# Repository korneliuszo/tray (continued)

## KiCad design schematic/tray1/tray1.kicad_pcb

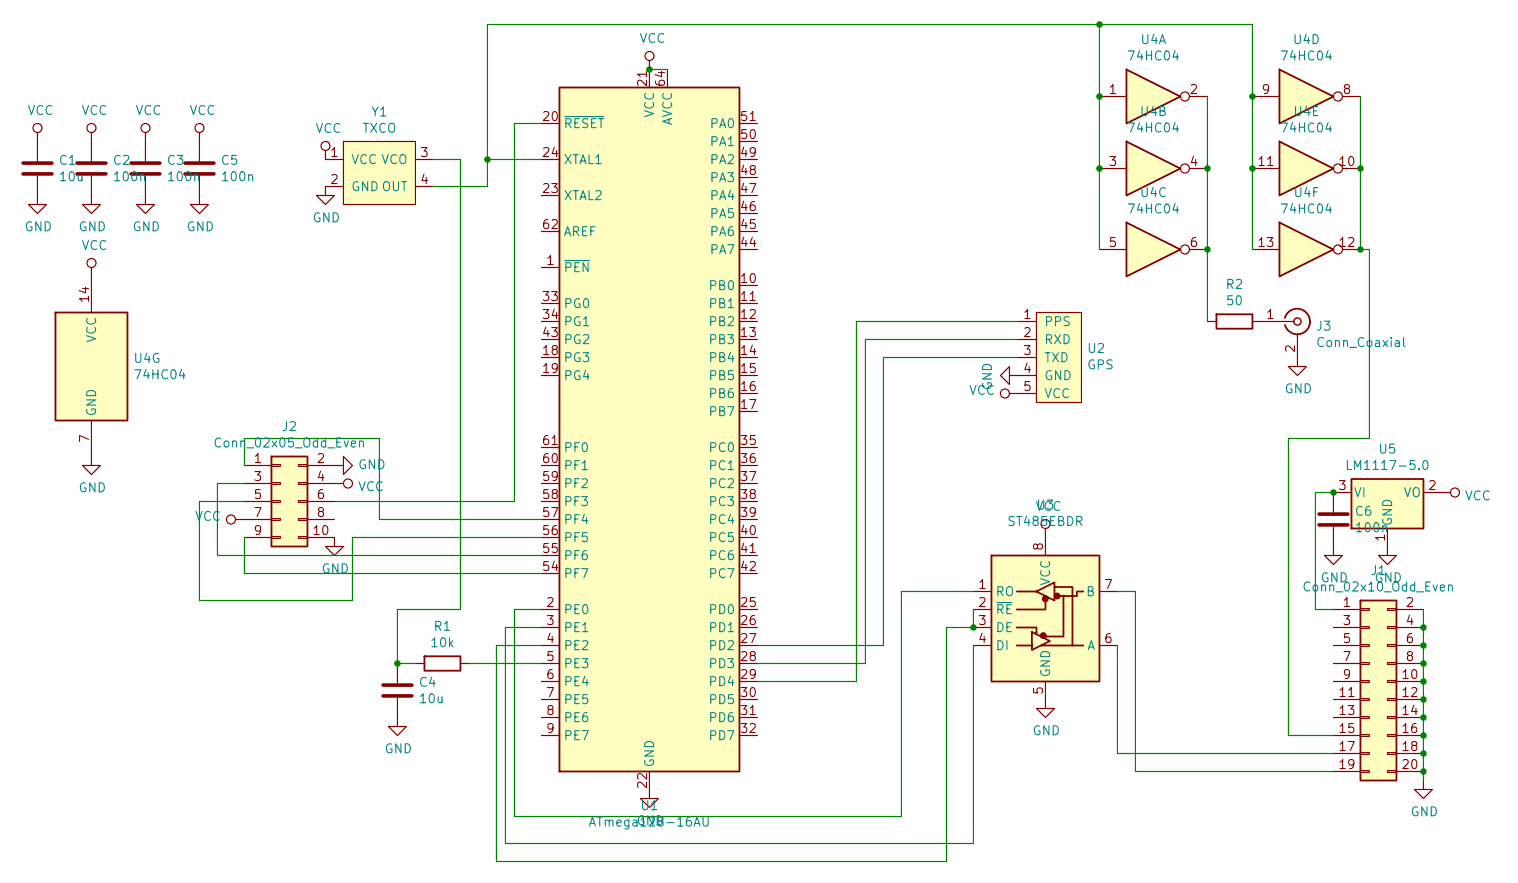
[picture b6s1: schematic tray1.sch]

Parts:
C1, C4: 10u; C_0805_2012Metric
C2, C3, C5: 100n; C_0805_2012Metric
C6: 100n; C_0805_2012Metric_Pad1.15x1.40mm_HandSolder
J1: Conn_02x10_Odd_Even; IDC-Header_2x10_P2.54mm_Horizontal
J2: Conn_02x05_Odd_Even; IDC-Header_2x05_P2.54mm_Vertical
J3: Conn_Coaxial; BNC_Amphenol_B6252HB-NPP3G-50_Horizontal
R1: 10k; R_0805_2012Metric
R2: 50; R_0805_2012Metric
U1: ATmega128-16AU; TQFP-64_14x14mm_P0.8mm
U2: GPS
U3: ST485EBDR; SOIC-8_3.9x4.9mm_P1.27mm
U4: 74HC04; SOIC-14_3.9x8.7mm_P1.27mm
U5: LM1117-5.0; SOT-223-3_TabPin2
Y1: TXCO; TCXO

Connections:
GND: C1.2, C2.2, C3.2, C4.2, C5.2, C6.2, J1.2, J1.4, J1.6, J1.8, J1.10, J1.12, J1.14, J1.16, J1.18, J1.20, J2.2, J2.10, J3.2 (Ext), U1.22 (GND), U1.53 (GND), U1.63 (GND), U2.4 (GND), U3.5 (GND), U4.7 (GND), U5.1 (GND), Y1.2 (GND)
unnamed: C4.1, R1.2, Y1.3 (VCO)
unnamed: C6.1, J1.1, U5.3 (VI)
unnamed: J1.15, U4.8, U4.10, U4.12
unnamed: J1.17, U3.6 (A)
unnamed: J1.19, U3.7 (B)
unnamed: J2.1, U1.57 (PF4)
unnamed: J2.3, U1.55 (PF6)
unnamed: J2.5, U1.56 (PF5)
unnamed: J2.6, U1.20 (~RESET)
unnamed: J2.9, U1.54 (PF7)
unnamed: J3.1 (In), R2.1
unnamed: R1.1, U1.5 (PE3)
unnamed: R2.2, U4.2, U4.4, U4.6
unnamed: U1.2 (PE0), U3.1 (RO)
unnamed: U1.3 (PE1), U3.4 (DI)
unnamed: U1.4 (PE2), U3.2 (~RE), U3.3 (DE)
unnamed: U1.24 (XTAL1), U4.1, U4.3, U4.5, U4.9, U4.11, U4.13, Y1.4 (OUT)
unnamed: U1.27 (PD2), U2.3 (TXD)
unnamed: U1.28 (PD3), U2.2 (RXD)
unnamed: U1.29 (PD4), U2.1 (PPS)
VCC: C1.1, C2.1, C3.1, C5.1, J2.4, J2.7, U1.21 (VCC), U1.52 (VCC), U1.64 (AVCC), U2.5 (VCC), U3.8 (VCC), U4.14 (VCC), U5.2 (VO), Y1.1 (VCC)

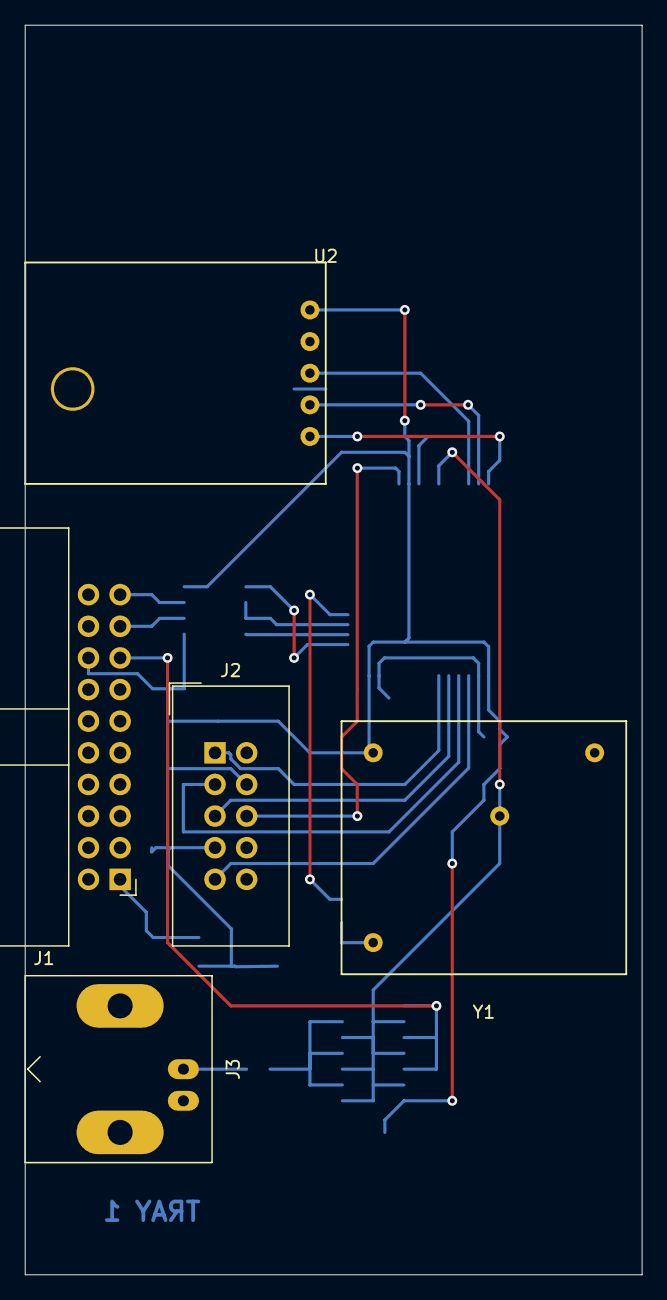
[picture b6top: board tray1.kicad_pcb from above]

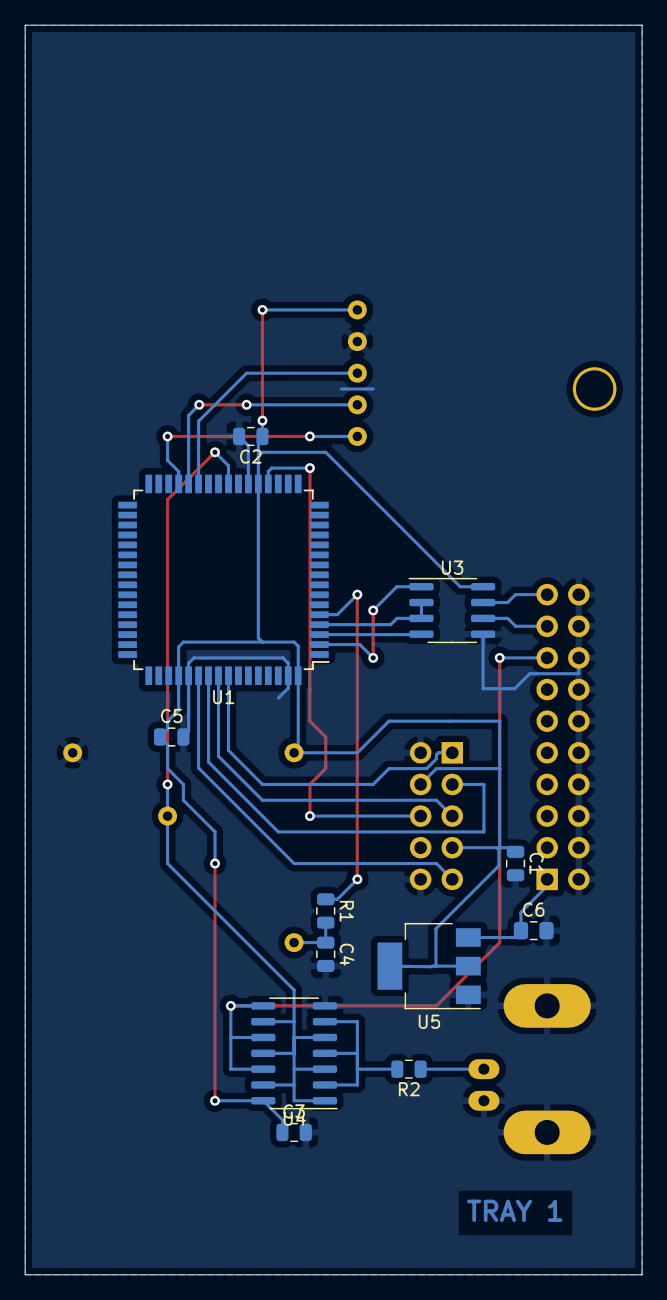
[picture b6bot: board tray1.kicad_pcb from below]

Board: 2 copper layers, 49.5 x 100.3 mm, 17 parts (12 on the bottom side), 22 nets.

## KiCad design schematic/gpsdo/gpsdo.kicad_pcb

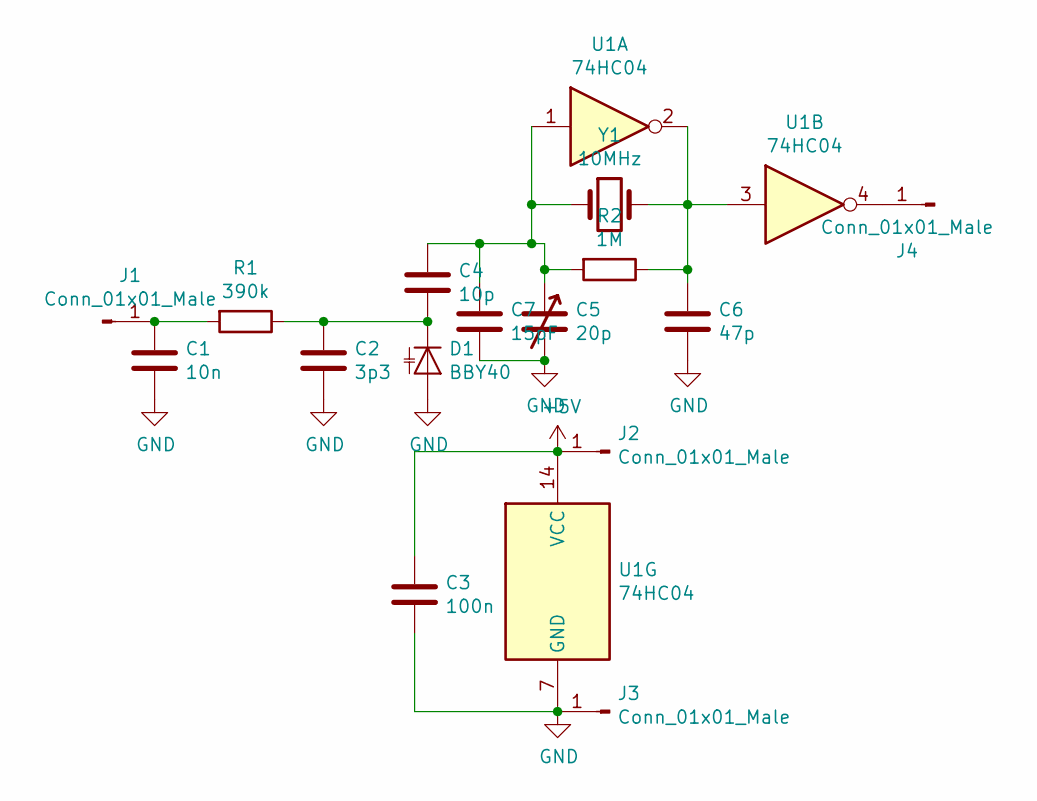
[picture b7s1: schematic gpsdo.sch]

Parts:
C1: 10n; C_0805_2012Metric_Pad1.15x1.40mm_HandSolder
C2: 3p3; C_0805_2012Metric_Pad1.15x1.40mm_HandSolder
C3: 100n; C_0805_2012Metric_Pad1.15x1.40mm_HandSolder
C4: 10p; C_0805_2012Metric_Pad1.15x1.40mm_HandSolder
C5: 20p; TerminalBlock_bornier-2_P5.08mm
C6: 47p; C_0805_2012Metric_Pad1.15x1.40mm_HandSolder
C7: 15pF; C_0805_2012Metric_Pad1.15x1.40mm_HandSolder
D1: BBY40; D_SOT-23_ANK
J1, J2, J3, J4: Conn_01x01_Male; PinHeader_1x01_P2.54mm_Vertical
R1: 390k; R_0805_2012Metric_Pad1.15x1.40mm_HandSolder
R2: 1M; R_0805_2012Metric_Pad1.15x1.40mm_HandSolder
U1: 74HC04; SOIC-14_3.9x8.7mm_P1.27mm
Y1: 10MHz; Crystal_HC49-U_Horizontal

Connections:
+5V: C3.1, J2.1, U1.14 (VCC)
GND: C1.2, C2.2, C3.2, C5.2, C6.2, C7.2, D1.2 (A), J3.1, U1.7 (GND)
unnamed: C1.1, J1.1, R1.2
unnamed: C2.1, C4.2, D1.1 (K), R1.1
unnamed: C4.1, C5.1, C7.1, R2.2, U1.1, Y1.1
unnamed: C6.1, R2.1, U1.2, U1.3, Y1.2
unnamed: J4.1, U1.4

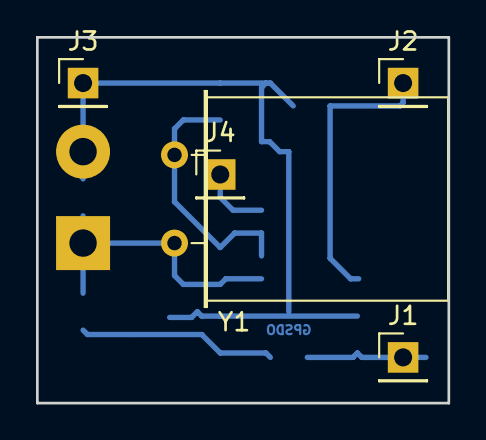
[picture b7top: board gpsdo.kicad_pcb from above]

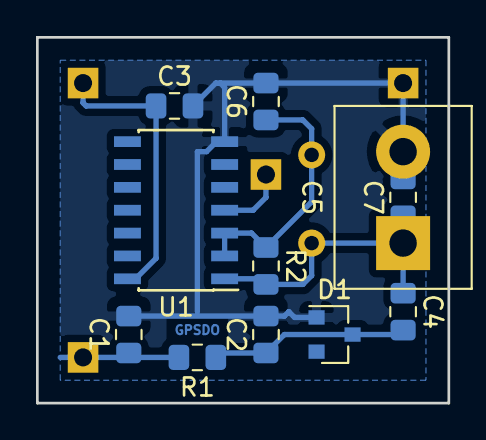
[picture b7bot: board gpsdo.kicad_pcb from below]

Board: 2 copper layers, 22.9 x 20.3 mm, 16 parts (11 on the bottom side), 7 nets.

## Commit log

2019-12-24 Add schematics
2020-04-06 Initial fw commit
    * working tlay2
    * working tray0
    * working bootloader on tray1
2020-04-06 Move schematics
2020-04-06 Add gitignore
2020-04-06 Be sure nobody overwrites us, and send reply.
2020-04-06 used so lto don't drop get_mcusr
2020-04-07 Fix program
2020-04-07 Asynchronous usbrouter
2020-04-07 tlay2_boot_mode is tlay2_ff thing
2020-04-07 Skeleton of tray1 firmware
2020-04-07 Remove unneeded header
2020-04-07 Pipe data from GPS
2020-04-07 Add schematics in pdf
2020-04-07 Use proper header
2020-04-08 Add oscillator measurement/adjustment
2020-04-08 Add text on board to satisfy pcb fab
2020-04-08 Add warning
2020-04-08 Update pcb to fix issue
2020-04-08 Initial tray2 commit
2020-04-08 Add gnd to oe pin
2020-04-08 Fix divisor so it is divisible without remainder
2020-04-08 Add frequency meter
2020-04-08 Change transistor with bigger fT
2020-04-14 Add measure command
2020-04-15 F_CPU is uint type, change it to int type in macro
2020-04-15 Update GPSDO schematic to used values
2020-04-15 Auto tuning crystal
2020-04-18 Add separate regulator for low noise
2020-04-18 Ignore first sample in auto mode
2020-04-18 If diff out of any sensible range, reset algorithm
2020-04-20 too much f
2020-04-20 Remove warning
2020-04-22 Add capacitor on path of clock
2020-04-22 Use 100 resistor instead capacitor
2020-04-25 Use tested MB506 prescaler
2020-04-27 In HF change resistor so it works better with CMOS inputs - now working up to 100MHz before 90MHz
2020-08-11 Refill
2020-08-16 Move components so they don't mashup with holding rail
2020-09-07 First measure don't return garbage
2020-09-07 Use selectable prescaler
2020-09-07 Allow putting hex value in program utility
2020-09-08 Add tray3 schematics
2020-09-08 Add tray3 code
2020-10-07 Fix mcu name
2020-10-07 Use ar with lto plugin
2020-10-07 Divide line for different targets
2020-10-14 Tray4
2020-10-14 Tray5 - for now only bootloader
2020-10-14 Add delay so it flashes stock uc
2020-10-14 Add notes
2020-10-15 fix fractional measurement
2020-10-15 Add tray3 schematics in pdf
2020-10-18 Add capacitors to board and change power connector to used by beefier PSU
